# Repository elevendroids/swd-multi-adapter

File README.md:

# SWD Multi Adapter

A handy embedded debugging interface adapter.

This simple board allows you to easily convert your SWD programming/debugging cables between:

- STDC14 - 14-pin connector commonly used in ST-Link debuggers and larger STM32-based boards
- ARM/JTAG - "legacy" 20 pin JTAG/SWD connector
- 0.05" 10-pin SWD - compact debugging/programming port
- 0.1" 10-pin SWD - DIY-friendly version of the above

Board designed in KiCad 5.1.6

Schematic: [PDF](docs/swd-multi-adapter.pdf)

License: [CC BY-SA 4.0](https://creativecommons.org/licenses/by-sa/4.0/)

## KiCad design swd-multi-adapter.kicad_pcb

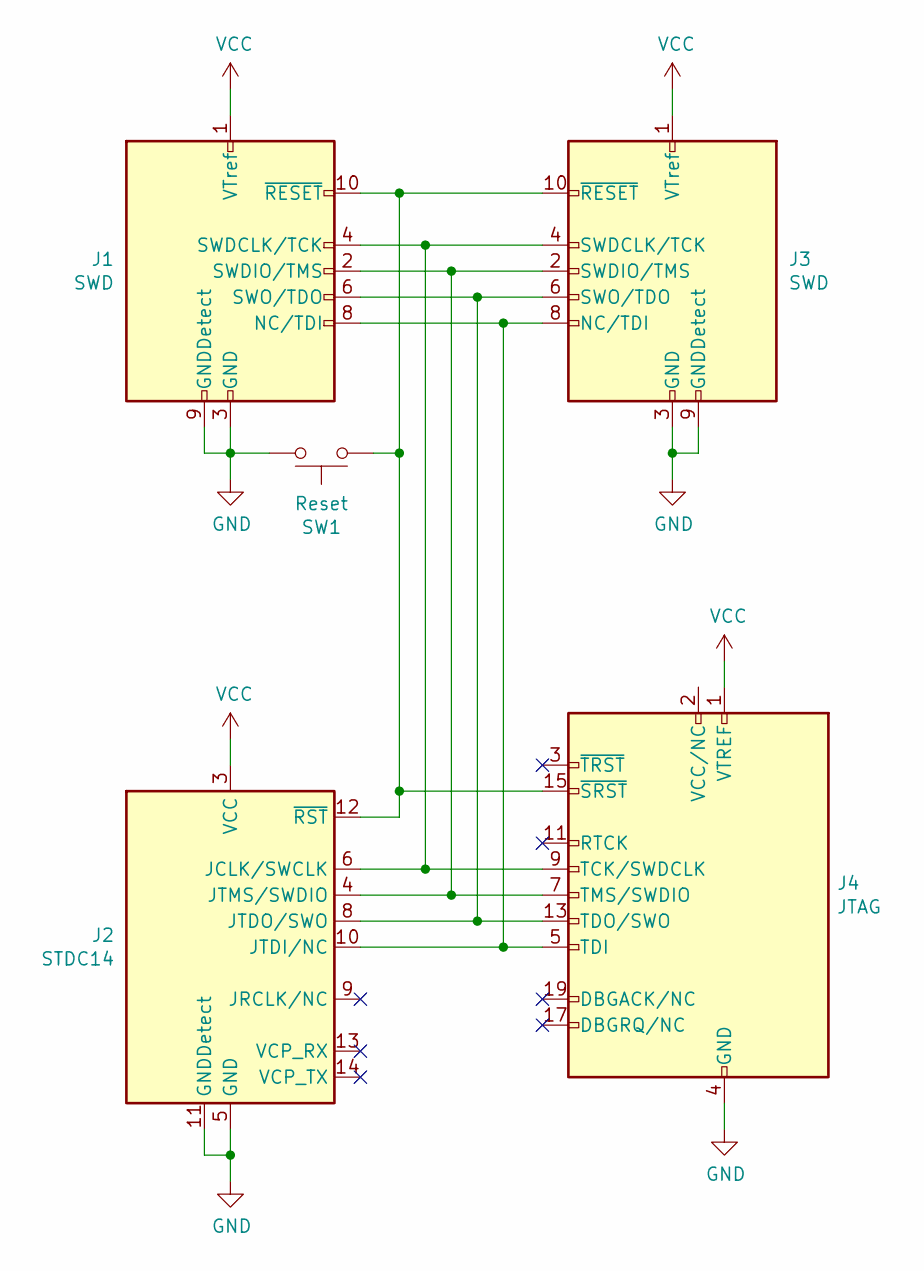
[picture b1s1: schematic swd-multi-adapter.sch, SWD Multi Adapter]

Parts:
J1: SWD; PinHeader_2x05_P1.27mm_Vertical_SMD
J2: STDC14; IDC-Header_2x07_P2.54mm_Vertical
J3: SWD; IDC-Header_2x05_P2.54mm_Vertical
J4: JTAG; IDC-Header_2x10_P2.54mm_Vertical
SW1: Reset; SW_SPST_CK_RS282G05A3

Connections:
GND: J1.3 (GND), J1.5 (GND), J1.9 (GNDDetect), J2.5 (GND), J2.7 (GND), J2.11 (GNDDetect), J3.3 (GND), J3.5 (GND), J3.9 (GNDDetect), J4.4 (GND), J4.6 (GND), J4.8 (GND), J4.10 (GND), J4.12 (GND), J4.14 (GND), J4.16 (GND), J4.18 (GND), J4.20 (GND), SW1.1
unnamed: J1.2 (SWDIO/TMS), J2.4 (JTMS/SWDIO), J3.2 (SWDIO/TMS), J4.7 (TMS/SWDIO)
unnamed: J1.4 (SWDCLK/TCK), J2.6 (JCLK/SWCLK), J3.4 (SWDCLK/TCK), J4.9 (TCK/SWDCLK)
unnamed: J1.6 (SWO/TDO), J2.8 (JTDO/SWO), J3.6 (SWO/TDO), J4.13 (TDO/SWO)
unnamed: J1.8 (NC/TDI), J2.10 (JTDI/NC), J3.8 (NC/TDI), J4.5 (TDI)
unnamed: J1.10 (~RESET~), J2.12 (~RST), J3.10 (~RESET~), J4.15 (~SRST~), SW1.2
VCC: J1.1 (VTref), J2.3 (VCC), J3.1 (VTref), J4.1 (VTREF)

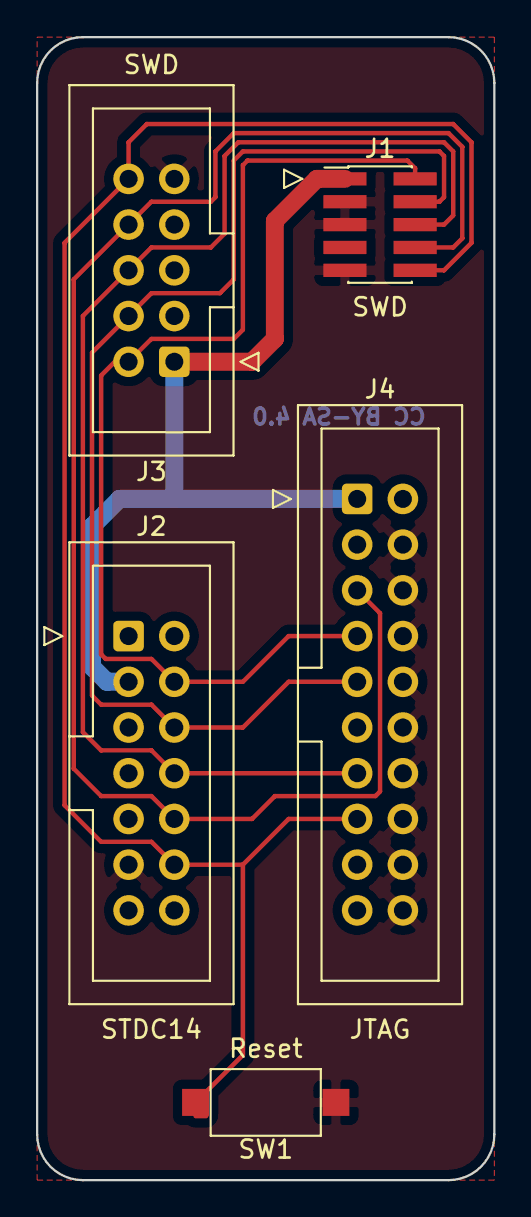
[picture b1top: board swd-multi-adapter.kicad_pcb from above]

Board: 2 copper layers, 25.4 x 63.5 mm, 5 parts (0 on the bottom side), 7 nets.

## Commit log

2020-07-27 Added board render, schematic PDF and a crude README
2020-07-27 README fixup
2020-07-27 Added license info
2020-07-27 README fixup (again)
2020-07-27 Added licensing info to the project files

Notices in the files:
swd-multi-adapter.kicad_pcb:
Released under the Creative Commons
© 2020 Michal Potrzebicz
